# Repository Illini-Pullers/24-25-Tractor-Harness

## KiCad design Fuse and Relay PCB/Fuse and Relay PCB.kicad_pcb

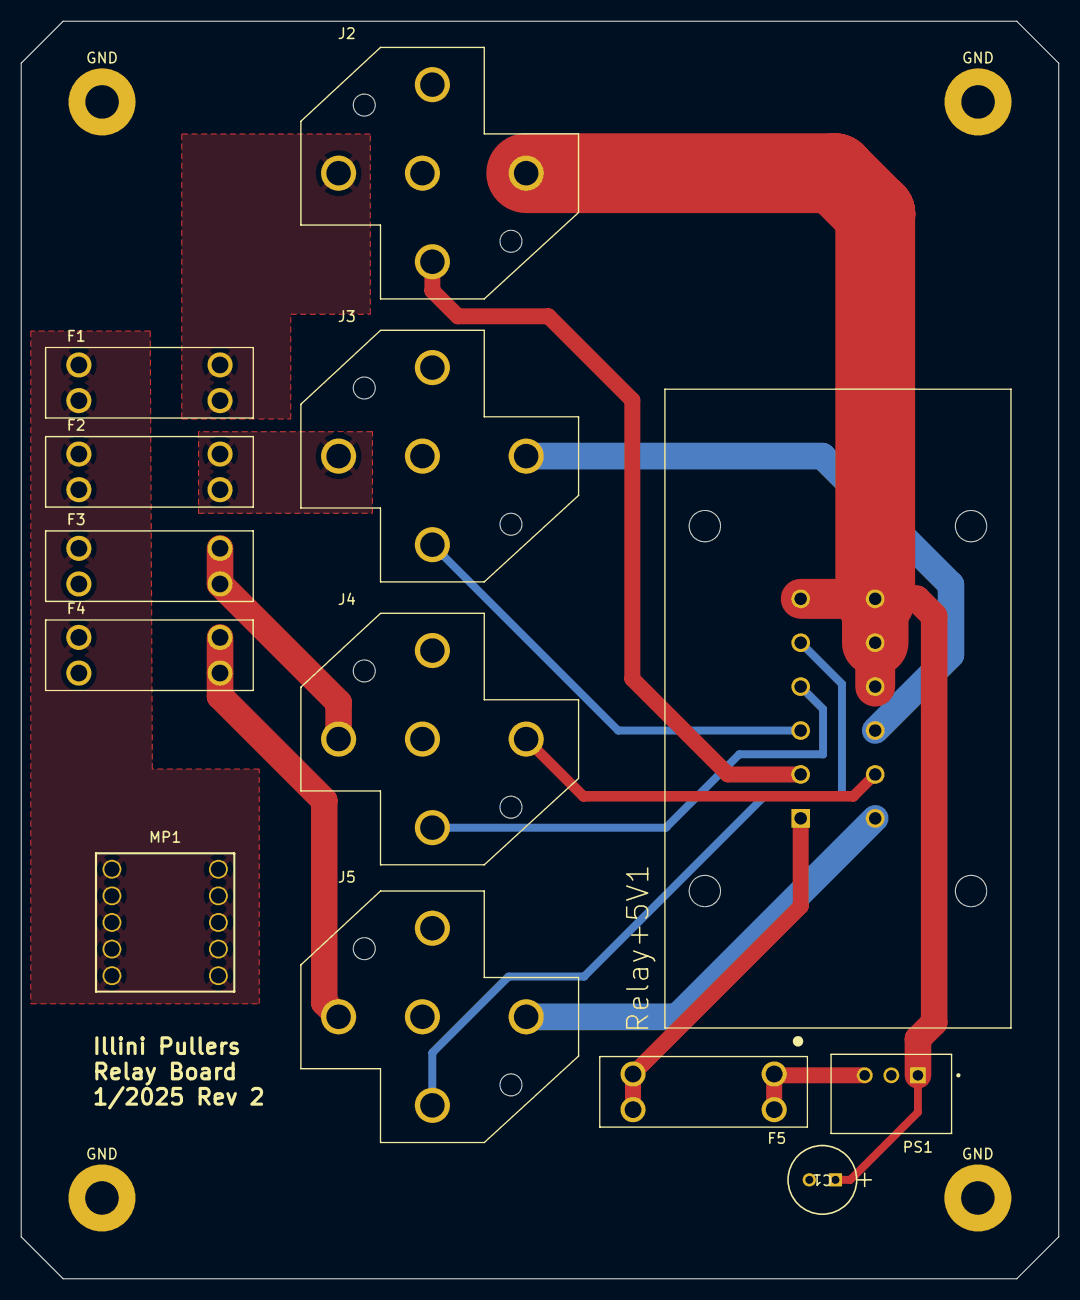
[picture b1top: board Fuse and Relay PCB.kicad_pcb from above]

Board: 2 copper layers, 99.0 x 120.0 mm, 17 parts (0 on the bottom side), 16 nets.

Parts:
C1: UVP1H100MED; U1-I_NCH
F1, F2, F3, F4, F5: 3557-15; FUSE_3557-15
GND: MountingHole_3.2mm_M3_Pad
GND#2, GND#3, GND#4: MountingHole_3.2mm_M3_Pad
J2, J3, J4, J5: VCF4-1000; TE_VCF4-1000
MP1: WP-RATR; WP-RATR_7461108_HAL
PS1: R-789.0-0.5; CONV_R-789.0-0.5
Relay+5V1: DTM15-12PA; TE_DTM15-12PA

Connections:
+12V: F1.1_1, F1.1_2, F2.1_1, F2.1_2, F3.1_1, F4.1_1, MP1.1, MP1.2, MP1.3, MP1.4, MP1.5, MP1.6, MP1.7, MP1.8, MP1.9, MP1.10
GND: C1.2, GND.1, GND#2.1, GND#3.1, GND#4.1, J2.86, J2.87A, J3.86, J3.87A, J4.86, J4.87A, J5.86, J5.87A, PS1.2 (GND)
unnamed: F1.2_1, F1.2_2, J2.87
unnamed: F2.2_1, F2.2_2, J3.87
unnamed: F3.2_1, F3.2_2, J4.87
unnamed: F4.2_1, F4.2_2, J5.87
unnamed: F5.2_1, F5.2_2, Relay+5V1.1
unnamed: C1.1, J2.30, PS1.1 (+VIN), Relay+5V1.6, Relay+5V1.7, Relay+5V1.8, Relay+5V1.9
unnamed: J2.85, Relay+5V1.2
unnamed: J3.30, Relay+5V1.10
unnamed: J3.85, Relay+5V1.3
unnamed: J4.30, Relay+5V1.11
unnamed: J4.85, Relay+5V1.4
unnamed: J5.30, Relay+5V1.12
unnamed: J5.85, Relay+5V1.5
unnamed: F5.1_1, F5.1_2, PS1.3 (+VOUT)

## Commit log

2025-01-27 Relay PCB Final
    KiCad files for relay PCB along with associated design footprints.
2025-01-30 Relay Board V2 (Actual final)
